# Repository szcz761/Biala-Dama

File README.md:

# Biala-Dama
Robot klasy minisumo tworzony przez:  Szymona Czaje i Marka Żyśko

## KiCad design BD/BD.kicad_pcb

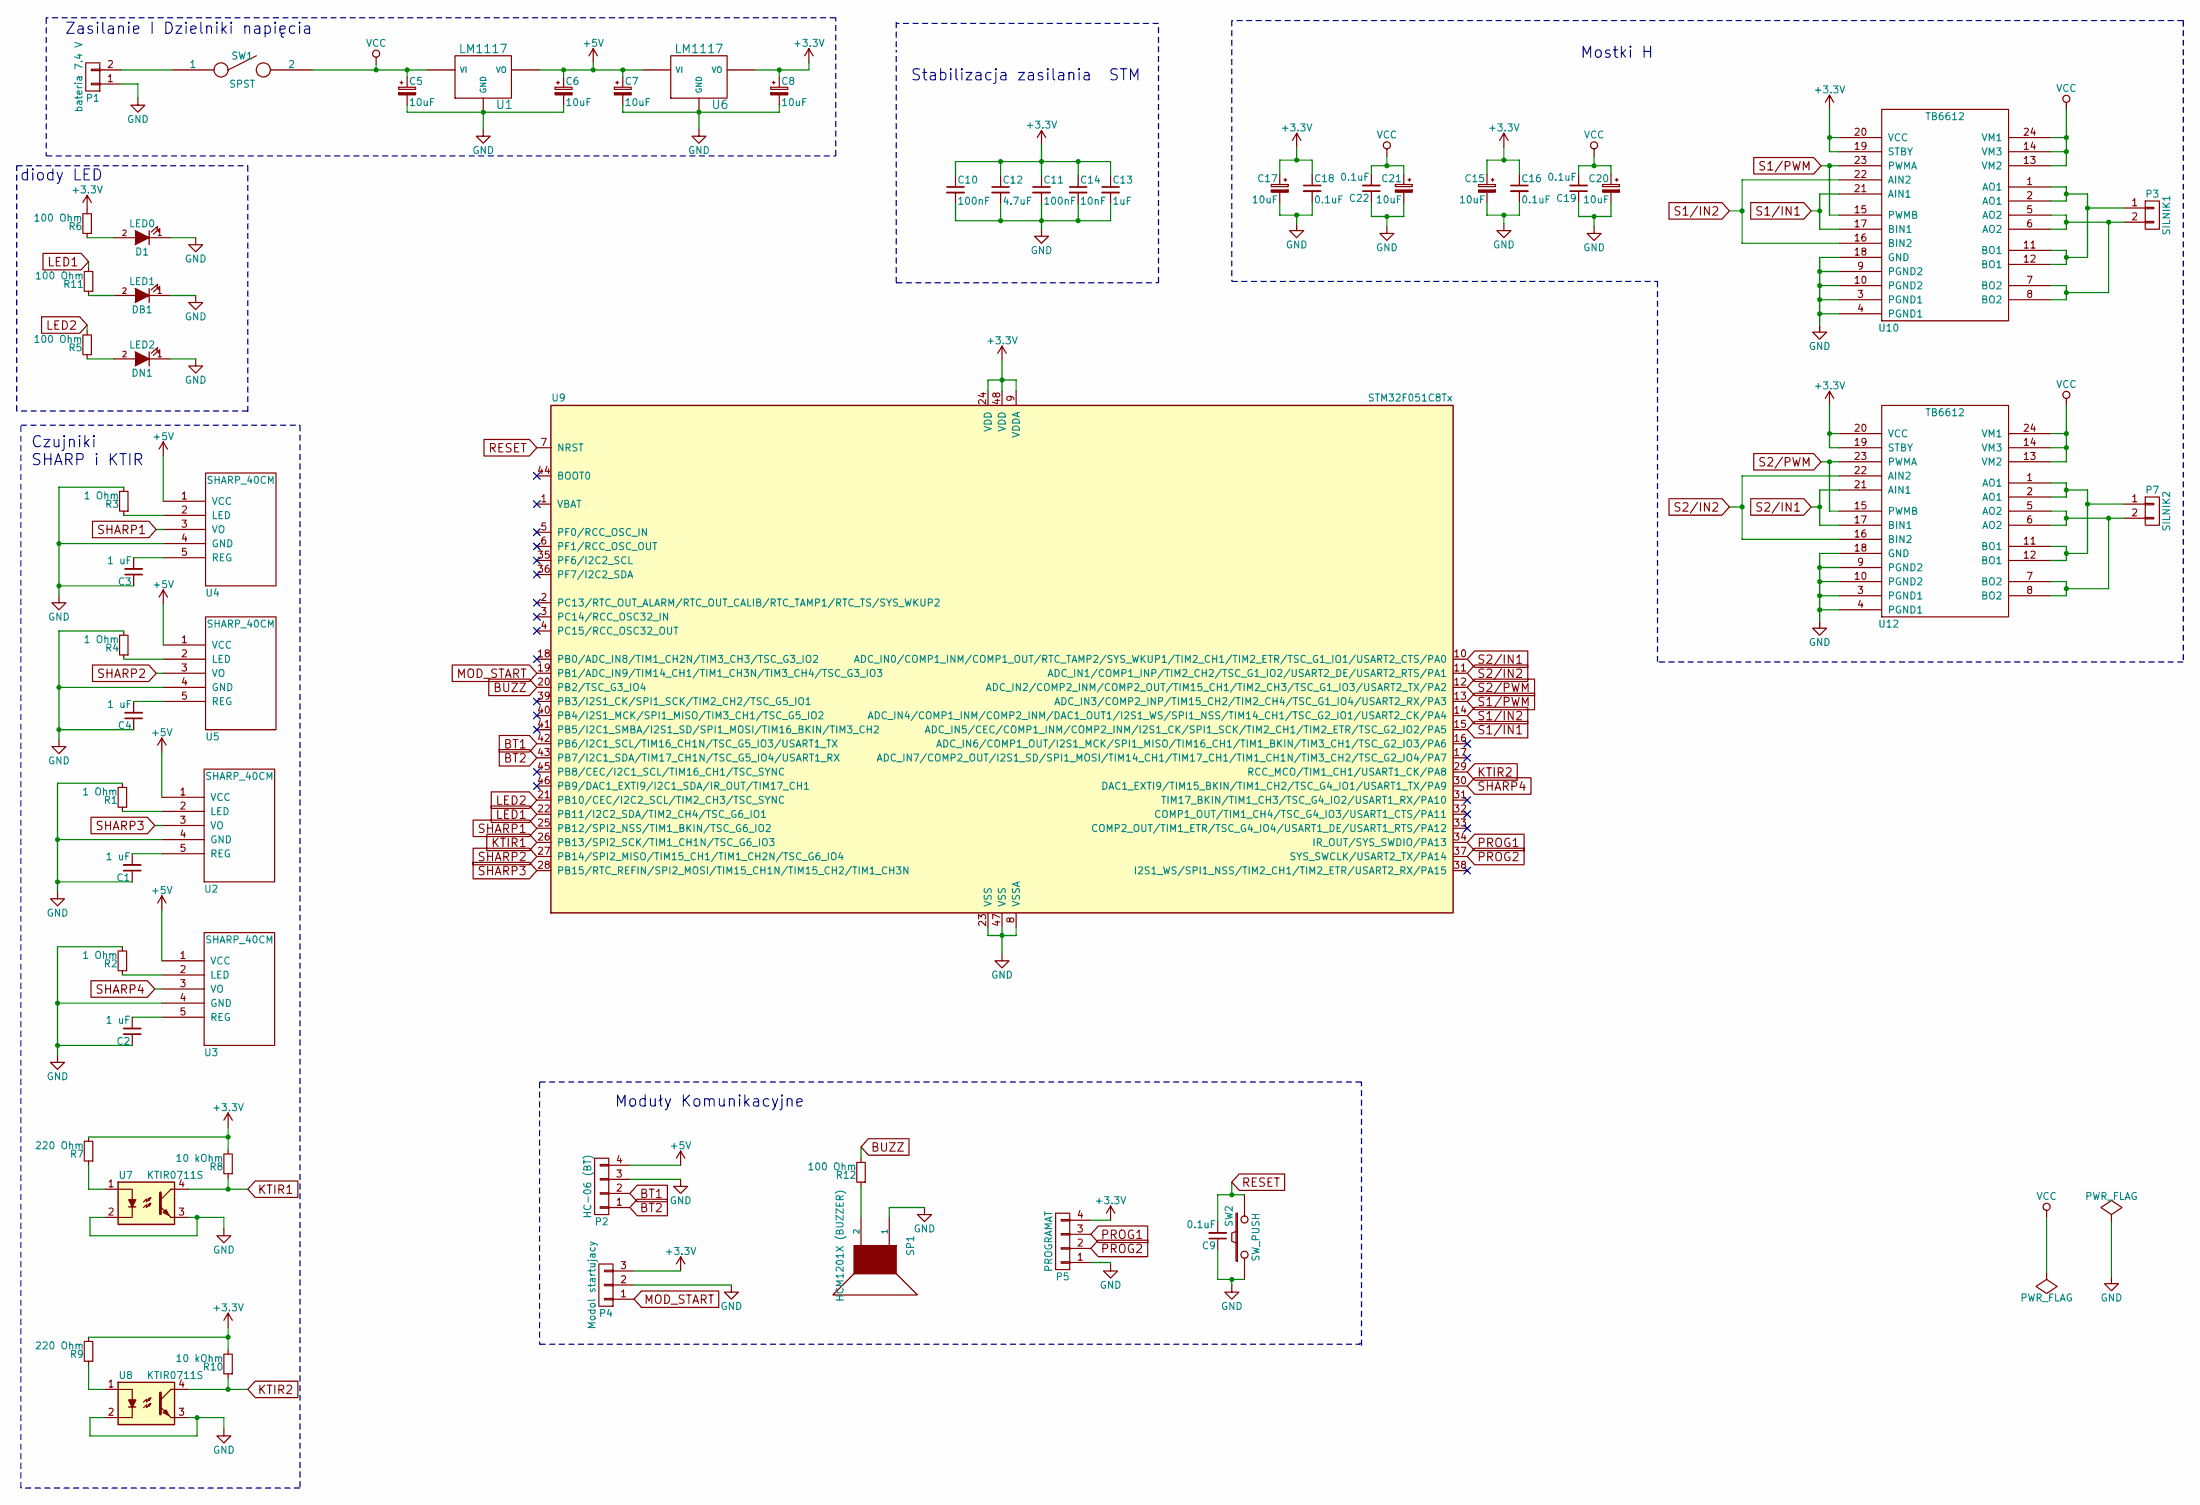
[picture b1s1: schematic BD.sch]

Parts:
C1, C2, C3, C4: 1 uF; C_0805_HandSoldering
C5, C6, C7, C8, C15, C17, C20, C21: 10uF; Tantalum_Case-A_EIA-3216-18_Hand
C9, C16, C18, C19, C22: 0.1uF; C_0805_HandSoldering
C10, C11: 100nF; C_0603_HandSoldering
C12: 4.7uF; C_0603_HandSoldering
C13: 1uF; C_0805_HandSoldering
C14: 10nF; C_0805_HandSoldering
D1: LED0; LED-5MM
DB1: LED1; LED-5MM
DN1: LED2; LED-5MM
P1: bateria 7.4 V; Socket_Strip_Straight_1x02
P2: HC-06 (BT); Socket_Strip_Straight_1x04
P3: SILNIK1; Socket_Strip_Straight_1x02
P4: Modol startujacy; Socket_Strip_Straight_1x03
P5: PROGRAMAT; Socket_Strip_Straight_1x04
P7: SILNIK2; Socket_Strip_Straight_1x02
R1, R2, R3, R4: 1 Ohm; R_0805_HandSoldering
R5, R6, R11, R12: 100 Ohm; R_0805_HandSoldering
R7, R9: 220 Ohm; R_0603_HandSoldering
R8, R10: 10 kOhm; R_0603_HandSoldering
SP1: HCM1201X (BUZZER); Buzzer_12x9.5RM7.6
SW1: SPST; SW_DIP_x1_Slide
SW2: SW_PUSH; SW_PUSH_6mm
U1, U6: LM1117; LM1117_SOT223
U2, U3, U4, U5: SHARP_40CM; GP2Y0D340K
U7, U8: KTIR0711S
U9: STM32F051C8Tx; STM32F051C8T6
U10, U12: TB6612

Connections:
+3V3: C8.1, C10.1, C11.1, C12.1, C13.1, C14.1, C15.1, C16.1, C17.1, C18.1, P4.3, P5.4, R6.2, R7.2, R8.2, R9.2, R10.2, U6.2 (VO), U9.9 (VDDA), U9.24 (VDD), U9.48 (VDD), U10.19 (STBY), U10.20 (VCC), U12.19 (STBY), U12.20 (VCC)
+5V: C6.1, C7.1, P2.4, U1.2 (VO), U2.1 (VCC), U3.1 (VCC), U4.1 (VCC), U5.1 (VCC), U6.1 (VI)
BT1: P2.2, U9.42 (PB6/I2C1_SCL/TIM16_CH1N/TSC_G5_IO3/USAR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)
BT2: P2.1, U9.43 (PB7/I2C1_SDA/TIM17_CH1N/TSC_G5_IO4/USAR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)
BUZZ: R12.2, U9.20 (PB2/TSC_G3_IO4)
GND: C1.1, C2.1, C3.1, C4.1, C5.2, C6.2, C7.2, C8.2, C9.1, C10.2, C11.2, C12.2, C13.2, C14.2, C15.2, C16.2, C17.2, C18.2, C19.1, C20.2, C21.2, C22.1, D1.1 (K), DB1.1 (K), DN1.1 (K), P1.1, P2.3, P4.2, P5.1, R1.2, R2.2, R3.2, R4.2, SP1.1, SW2.1, U1.3 (GND), U2.4 (GND), U3.4 (GND), U4.4 (GND), U5.4 (GND), U6.3 (GND), U7.2, U7.3, U8.2, U8.3, U9.8 (VSSA), U9.23 (VSS), U9.47 (VSS), U10.3 (PGND1), U10.4 (PGND1), U10.9 (PGND2), U10.10 (PGND2), U10.18 (GND), U12.3 (PGND1), U12.4 (PGND1), U12.9 (PGND2), U12.10 (PGND2), U12.18 (GND)
KTIR1: R8.1, U7.4, U9.26 (PB13/SPI2_SCK/TIM1_CH1N/TSC_G6_IO3)
KTIR2: R10.1, U8.4, U9.29 (RCC_MCO/TIM1_CH1/USART1_CK/PA8)
LED1: R11.2, U9.22 (PB11/I2C2_SDA/TIM2_CH4/TSC_G6_IO1)
LED2: R5.2, U9.21 (PB10/CEC/I2C2_SCL/TIM2_CH3/TSC_SYNC)
MOD_START: P4.1, U9.19 (PB1/ADC_IN9/TIM14_CH1/TIM1_CH3N/TIM3_CH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)
unnamed: C1.2, U2.5 (REG)
unnamed: C2.2, U3.5 (REG)
unnamed: C3.2, U4.5 (REG)
unnamed: C4.2, U5.5 (REG)
unnamed: D1.2 (A), R6.1
unnamed: DB1.2 (A), R11.1
unnamed: DN1.2 (A), R5.1
unnamed: P1.2, SW1.1
unnamed: P3.1, U10.1 (AO1), U10.2 (AO1), U10.11 (BO1), U10.12 (BO1)
unnamed: P3.2, U10.5 (AO2), U10.6 (AO2), U10.7 (BO2), U10.8 (BO2)
unnamed: P7.1, U12.1 (AO1), U12.2 (AO1), U12.11 (BO1), U12.12 (BO1)
unnamed: P7.2, U12.5 (AO2), U12.6 (AO2), U12.7 (BO2), U12.8 (BO2)
unnamed: R1.1, U2.2 (LED)
unnamed: R2.1, U3.2 (LED)
unnamed: R3.1, U4.2 (LED)
unnamed: R4.1, U5.2 (LED)
unnamed: R7.1, U7.1
unnamed: R9.1, U8.1
unnamed: R12.1, SP1.2
PROG1: P5.3, U9.34 (IR_OUT/SYS_SWDIO/PA13)
PROG2: P5.2, U9.37 (SYS_SWCLK/USART2_TX/PA14)
RESET: C9.2, SW2.2, U9.7 (NRST)
S1/IN1: U9.15 (ADC_IN5/CEC/COMP1_INM/COMP2_INM/I2S1_CK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), U10.17 (BIN1), U10.21 (AIN1)
S1/IN2: U9.14 (ADC_IN4/COMP1_INM/COMP2_INM/DAC1_OUT1/I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), U10.16 (BIN2), U10.22 (AIN2)
S1/PWM: U9.13 (ADC_IN3/COMP2_INP/TIM15_CH2/TIM2_CH4/TS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), U10.15 (PWMB), U10.23 (PWMA)
S2/IN1: U9.10 (ADC_IN0/COMP1_INM/COMP1_OUT/RTC_TAMP2/S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), U12.17 (BIN1), U12.21 (AIN1)
S2/IN2: U9.11 (ADC_IN1/COMP1_INP/TIM2_CH2/TSC_G1_IO2/U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), U12.16 (BIN2), U12.22 (AIN2)
S2/PWM: U9.12 (ADC_IN2/COMP2_INM/COMP2_OUT/TIM15_CH1/T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), U12.15 (PWMB), U12.23 (PWMA)
SHARP1: U4.3 (VO), U9.25 (PB12/SPI2_NSS/TIM1_BKIN/TSC_G6_IO2)
SHARP2: U5.3 (VO), U9.27 (PB14/SPI2_MISO/TIM15_CH1/TIM1_CH2N/TSC_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)
SHARP3: U2.3 (VO), U9.28 (PB15/RTC_REFIN/SPI2_MOSI/TIM15_CH1N/TIM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)
SHARP4: U3.3 (VO), U9.30 (DAC1_EXTI9/TIM15_BKIN/TIM1_CH2/TSC_G4_I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)
VCC: C5.1, C19.2, C20.1, C21.1, C22.2, SW1.2, U1.1 (VI), U10.13 (VM2), U10.14 (VM3), U10.24 (VM1), U12.13 (VM2), U12.14 (VM3), U12.24 (VM1)

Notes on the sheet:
Zasilanie I Dzielniki napięcia
diody LED
Czujniki SHARP i KTIR
Moduły Komunikacyjne
Mostki H
Stabilizacja zasilania STM

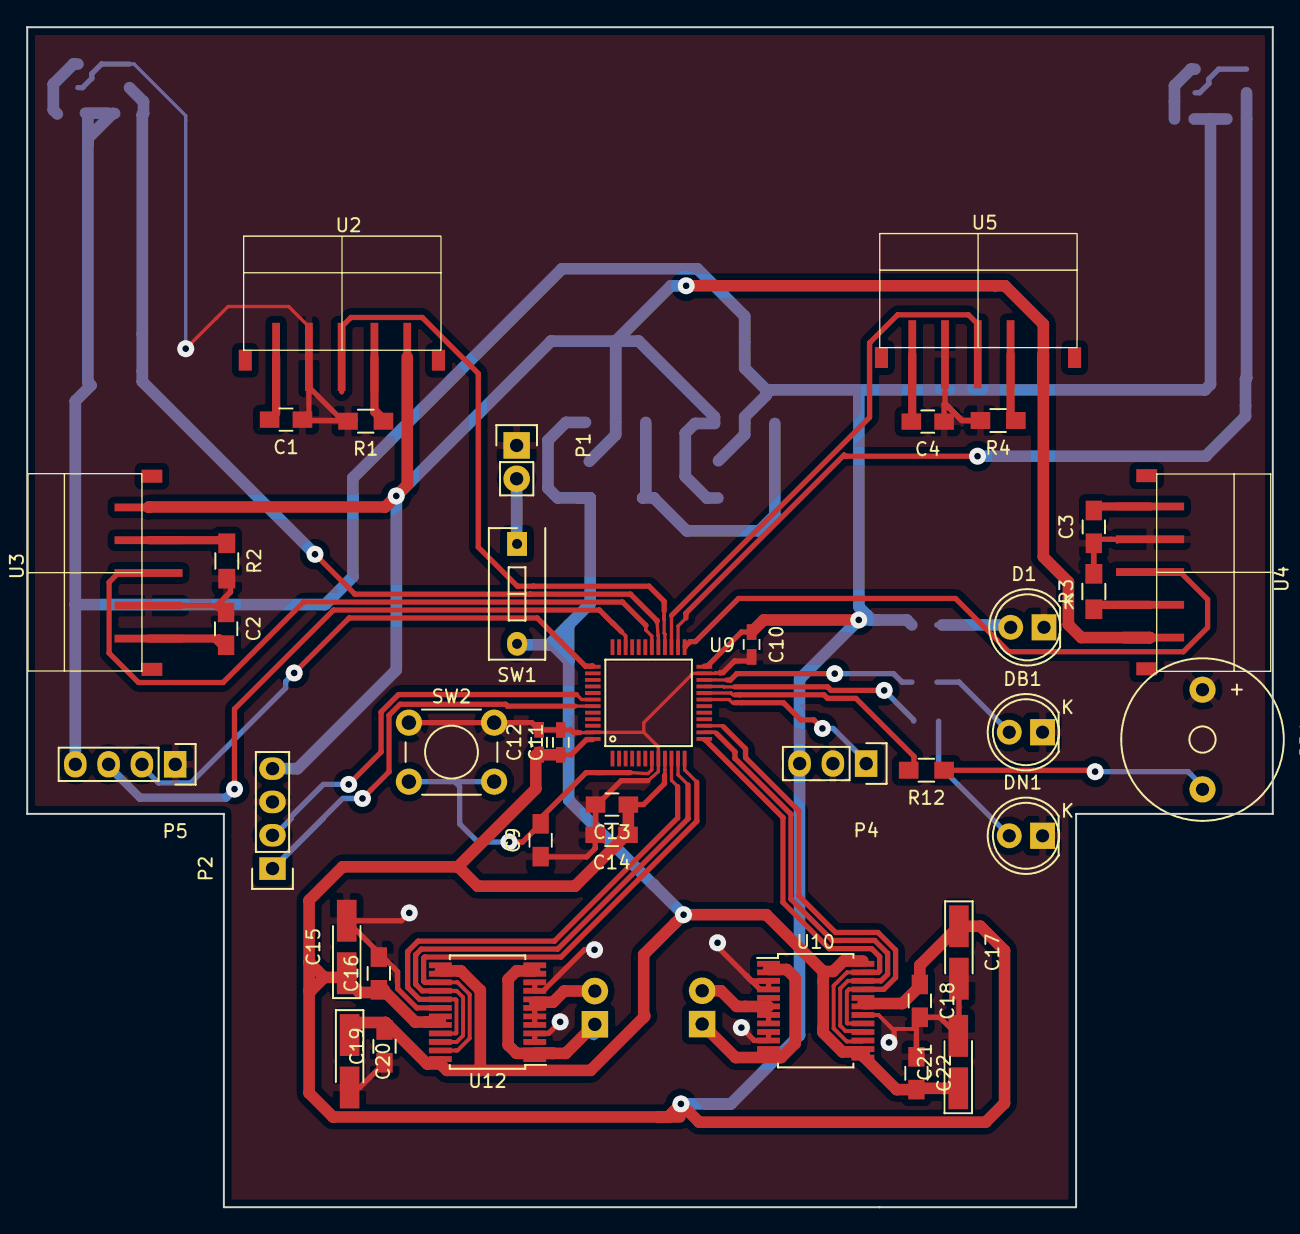
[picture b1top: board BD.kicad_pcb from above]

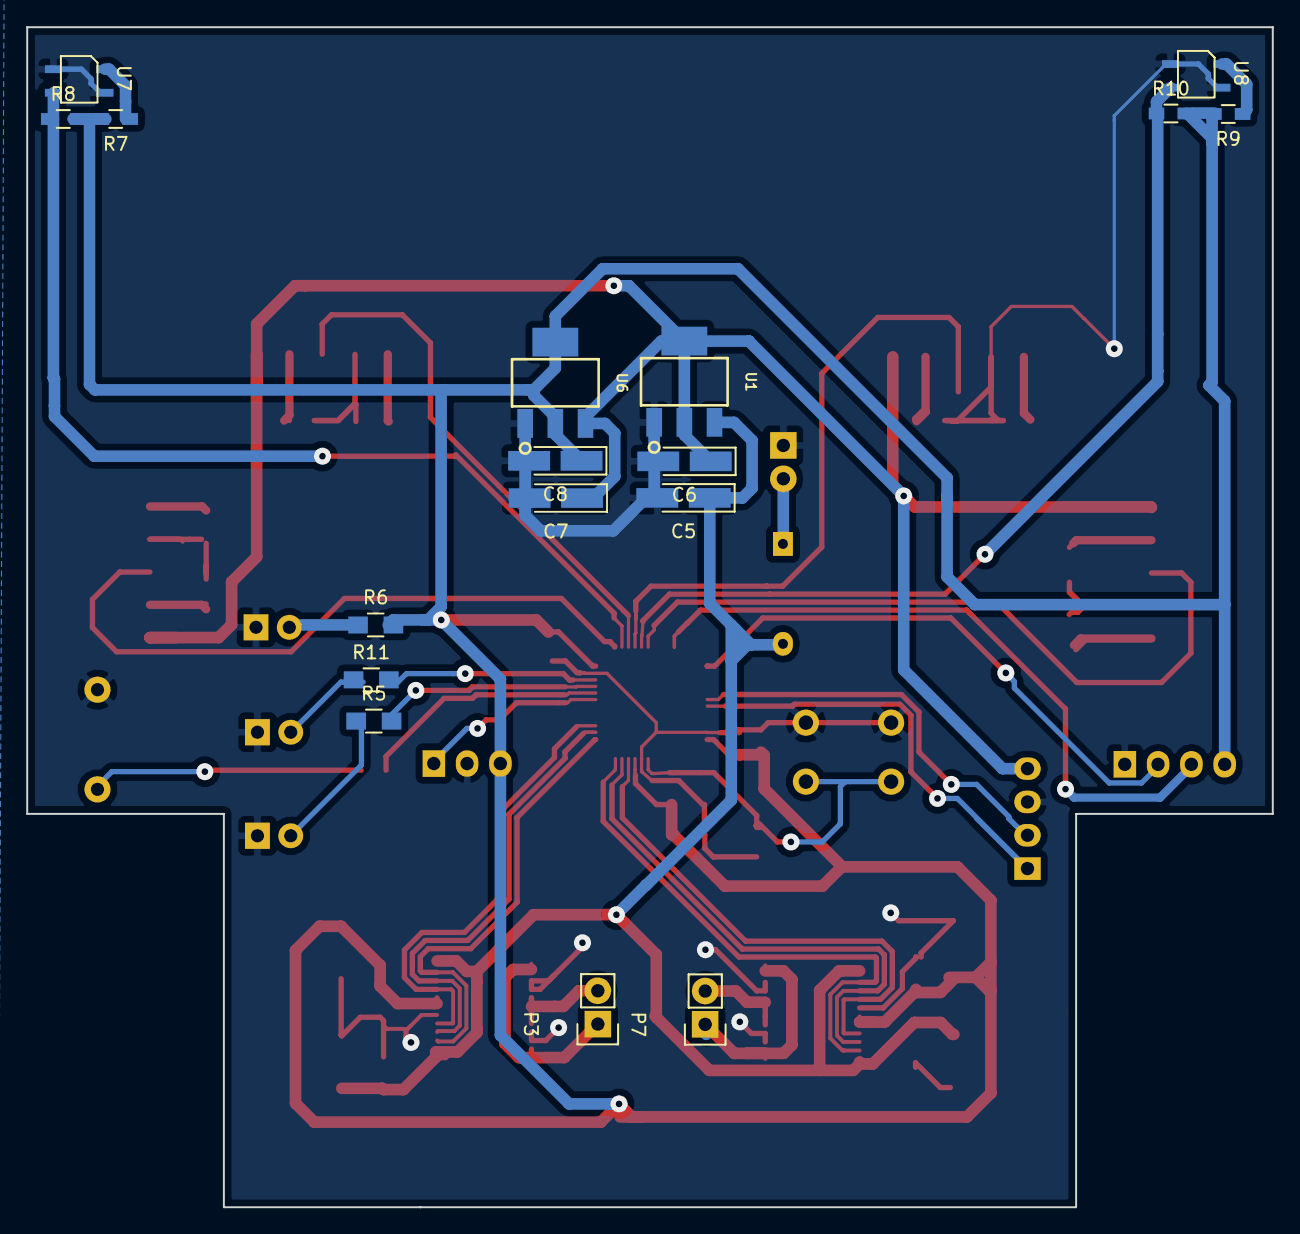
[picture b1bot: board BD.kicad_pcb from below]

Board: 2 copper layers, 95.0 x 90.0 mm, 57 parts (17 on the bottom side), 44 nets.

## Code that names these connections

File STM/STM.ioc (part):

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Mcu.Name=STM32F051C8Tx
Mcu.Package=LQFP48
Mcu.UserName=STM32F051C8Tx
PA0.GPIOParameters=GPIO_Label
PA0.GPIO_Label=S2/IN1
PA0.Signal=GPIO_Output
PA1.GPIOParameters=GPIO_Label
PA1.GPIO_Label=S2/IN2
PA1.Signal=GPIO_Output
PA13.GPIOParameters=GPIO_Label
PA13.GPIO_Label=PROG1
PA13.Mode=Serial_Wire
PA13.Signal=SYS_SWDIO
PA14.GPIOParameters=GPIO_Label
PA14.GPIO_Label=PROG2
PA14.Mode=Serial_Wire
PA14.Signal=SYS_SWCLK
PA2.GPIOParameters=GPIO_Label
PA2.GPIO_Label=S2/PWM
PA2.Signal=GPIO_Output
PA3.GPIOParameters=GPIO_Label
PA3.GPIO_Label=S1/PWM
PA3.Signal=GPIO_Output
PA4.GPIOParameters=GPIO_Label
PA4.GPIO_Label=S1/IN2
PA4.Signal=GPIO_Output
PA5.GPIOParameters=GPIO_Label
PA5.GPIO_Label=S1/IN1
PA5.Signal=GPIO_Output
PA8.GPIOParameters=GPIO_Label
PA8.GPIO_Label=KATIR2
PA8.Signal=GPIO_Input
PA9.GPIOParameters=GPIO_Label
PA9.GPIO_Label=SHARP4
PA9.Signal=GPIO_Input
PB1.GPIOParameters=GPIO_Label
PB1.GPIO_Label=MOD_START
PB1.Signal=GPIO_Input
PB10.GPIOParameters=GPIO_Label
PB10.GPIO_Label=LED2
PB10.Signal=GPIO_Output
PB11.GPIOParameters=GPIO_Label
PB11.GPIO_Label=LED1
PB11.Signal=GPIO_Output
PB12.GPIOParameters=GPIO_Label
PB12.GPIO_Label=SHARP1
PB12.Signal=GPIO_Input
PB13.GPIOParameters=GPIO_Label
PB13.GPIO_Label=KTIR1
PB13.Signal=GPIO_Input
PB14.GPIOParameters=GPIO_Label
PB14.GPIO_Label=SHARP2
PB14.Signal=GPIO_Input
PB15.GPIOParameters=GPIO_Label
PB15.GPIO_Label=SHARP3
PB15.Signal=GPIO_Input
PB2.GPIOParameters=GPIO_Label
PB2.GPIO_Label=BUZZ
PB2.Signal=GPIO_Output
PB6.GPIOParameters=GPIO_Label
PB6.GPIO_Label=BT2
PB6.Signal=USART1_TX
PB7.GPIOParameters=GPIO_Label
PB7.GPIO_Label=BT1
PB7.Signal=USART1_RX

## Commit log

2016-11-17 pierwsze zmiany
2016-11-17 Chyba Skończony schemat
2016-11-18 poprawka
2016-11-20 kosztorys/lista zakopow
2016-11-21 footprinty zrobione
2016-11-22 plytka_pcb
2016-11-23 można szyczyć?
2016-11-24 moze zadziala?
2016-11-24 koniec?
2016-11-29 tak?
2016-11-29 Zwiekszenie plytki
2016-11-29 Inventor wersja 1
2016-11-29 inventor teraz
2016-11-30 moze
2016-12-01 mozna drukowac?
2016-12-18 2 wersja plytek
2016-12-18 taak
2016-12-18 Stabilizatory na dnie
2016-12-18 Poprawilem jeszcze jedno polaczenie gnd,jest dobrze teraz, sprawdzaj
